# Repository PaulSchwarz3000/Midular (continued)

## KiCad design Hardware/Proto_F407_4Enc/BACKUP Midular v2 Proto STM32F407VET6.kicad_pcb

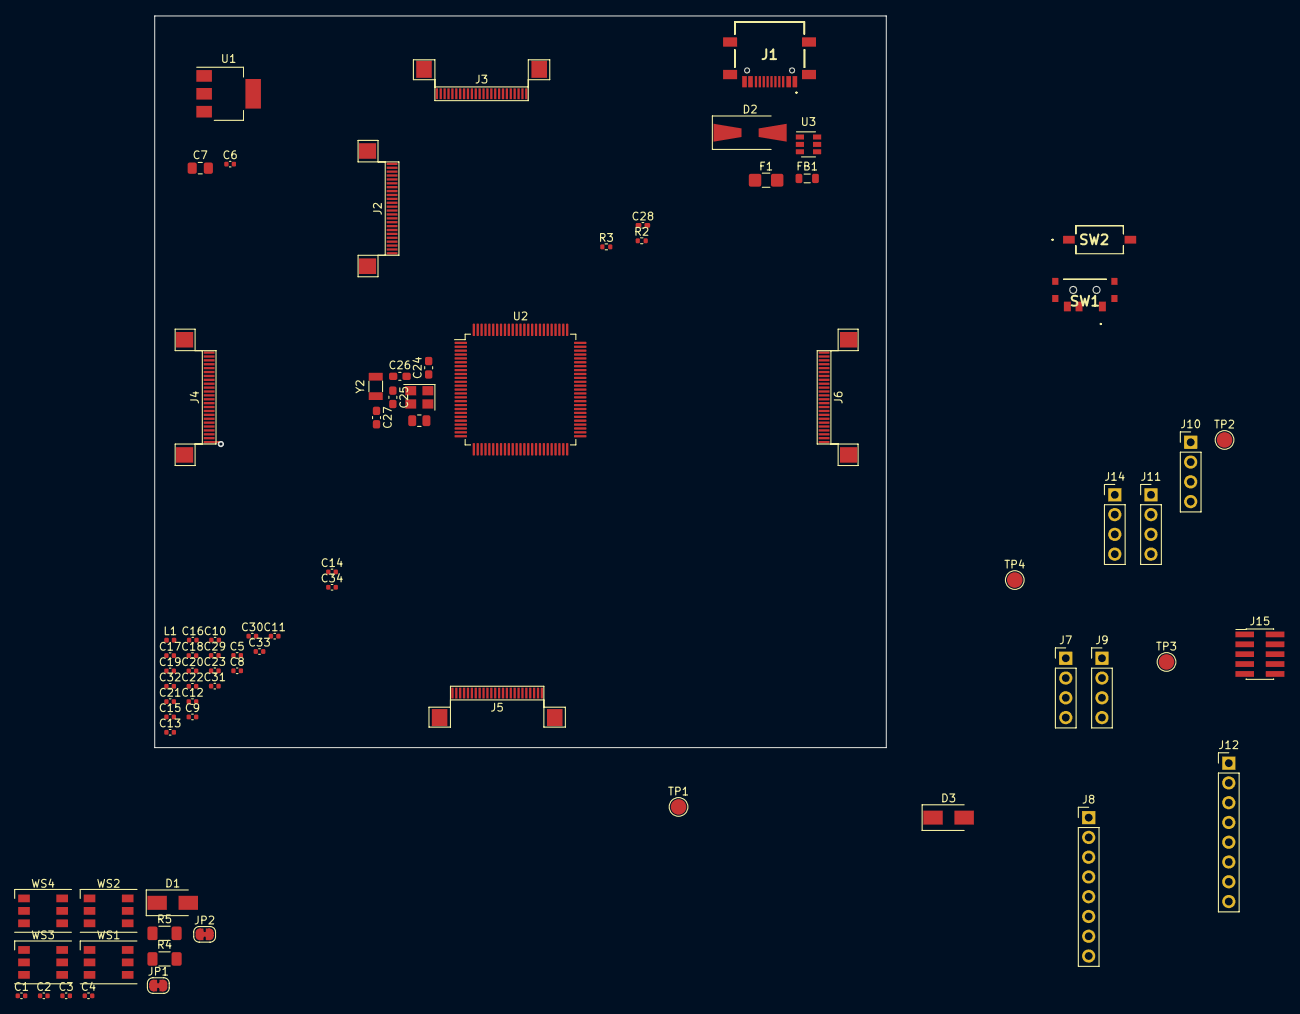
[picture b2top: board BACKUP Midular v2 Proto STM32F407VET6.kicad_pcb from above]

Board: 4 copper layers, 94.0 x 94.0 mm, 77 parts (1 on the bottom side), 75 nets.

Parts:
BAT1: CR2032-BS-6-1; CR2032BS61
C1, C2, C3, C4, C5, C9, C12, C16, C18, C20, C22, C29, C31: 100n; C_0402_1005Metric
C6, C8, C10, C11, C33, C34: 2u2; C_0402_1005Metric
C7: 10uF; C_0805_2012Metric_Pad1.18x1.45mm_HandSolder
C13, C15, C17, C19, C21, C23, C30: 10n; C_0402_1005Metric
C14: 1u; C_0402_1005Metric
C24, C25, C26, C27: 12p; C_0603_1608Metric_Pad1.08x0.95mm_HandSolder
C28: 10n; C_0402_1005Metric_Pad0.74x0.62mm_HandSolder
C32: 4u7; C_0402_1005Metric
D1: NC; D_SMA
D2: D_Schottky; D_SMA-SMB_Universal_Handsoldering
D3: M7; D_SMA
F1: Polyfuse 500mA; Fuse_1206_3216Metric_Castellated
FB1: GZ2012D601TF; L_0805_2012Metric
J1: USB_C_Receptacle_USB2.0; TYPEC304SACP16
J2, J3, J4, J5, J6: Conn_01x24; FPC_24_AFC24-S24FIC-00
J7, J9, J10, J11, J14: Conn_01x04; PinHeader_1x04_P2.54mm_Vertical
J8, J12: Conn_01x08; PinHeader_1x08_P2.54mm_Vertical
J15: Conn_ARM_JTAG_SWD_10; PinHeader_2x05_P1.27mm_Vertical_SMD
JP1, JP2: SolderJumper_2_Bridged; SolderJumper-2_P1.3mm_Bridged_RoundedPad1.0x1.5mm
L1: 39n; L_0402_1005Metric
R1: 220R; R_0805_2012Metric
R2, R3: 10k; R_0402_1005Metric
R4, R5: 1k1; R_1206_3216Metric_Pad1.30x1.75mm_HandSolder
SW1: SW_SPDT; SK3296S01L3
SW2: SW_SPST; K21107STA4SW06
TP1, TP2, TP3, TP4: TestPoint; TestPoint_Pad_D2.0mm
U1: AMS1117-3.3; SOT-223-3_TabPin2
U2: STM32F407VETx; LQFP-100_14x14mm_P0.5mm
U3: USBLC6-2SC6; SOT-23-6
WS1, WS2, WS3, WS4: WS2813; LED_WS2812_PLCC6_5.0x5.0mm_P1.6mm
Y1: 25MHz 12pF; Crystal_SMD_3225-4Pin_3.2x2.5mm
Y2: 32.768 kHz; Crystal_SMD_3215-2Pin_3.2x1.5mm

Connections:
+3V3: C7.1, C8.1, C15.2, C16.2, C17.2, C18.2, C19.2, C20.2, C21.2, C22.2, C23.2, C29.2, C30.2, C31.2, C32.2, C33.1, C34.1, J2.3, J2.22, J7.3, J8.2, J10.3, J11.3, J14.3, J15.1, JP1.1, L1.1, R3.2, SW1.1, TP3.1, U1.2, U2.11, U2.19, U2.28, U2.50, U2.75, U2.100
+5V: C5.1, C6.1, D1.2, D2.1, D3.2, J2.1, J2.24, J3.6, J3.7, J3.18, J3.19, J4.6, J4.7, J4.18, J4.19, J5.6, J5.7, J5.18, J5.19, J6.6, J6.7, J6.18, J6.19, J9.4, J12.8, JP2.1, TP4.1, U1.3, U3.5
+12V: J3.2, J3.4, J3.21, J3.23, J4.2, J4.4, J4.21, J4.23, J5.2, J5.4, J5.21, J5.23, J6.2, J6.4, J6.21, J6.23
BOOT0: R2.1, U2.94
CAN_Rx: J7.1, U2.81
CAN_Tx: J7.4, U2.82
CRx2: J4.16, U2.33
CRx3: J5.16, U2.57
CRx4: J6.16, U2.62
CTx1: J3.9, U2.90
CTx2: J4.9, U2.16
CTx3: J5.9, U2.54
CTx4: J6.9, U2.61
DAC_OUT1: J14.1, U2.29
DAC_OUT2: J14.4, U2.30
ENC1_A: J2.4, U2.77
ENC1_B: J2.6, U2.89
ENC2_A: J2.8, U2.31
ENC2_B: J2.10, U2.32
ENC3_A: J2.15, U2.59
ENC3_B: J2.17, U2.60
ENC4_A: J2.19, U2.23
ENC4_B: J2.21, U2.24
GND: BAT1.2, C1.1, C2.1, C3.1, C4.1, C5.2, C6.2, C7.2, C8.2, C9.2, C10.2, C11.2, C12.2, C13.2, C14.2, C15.1, C16.1, C17.1, C18.1, C19.1, C20.1, C21.1, C22.1, C23.1, C24.2, C25.2, C26.2, C27.2, C28.2, C29.1, C30.1, C31.1, C32.1, C33.2, C34.2, J1.A1, J1.A12, J1.B1, J1.B12, J2.2, J2.7, J2.11, J2.14, J2.18, J2.23, J3.1, J3.3, J3.5, J3.8, J3.10, J3.12, J3.13, J3.15, J3.17, J3.20, J3.22, J3.24, J4.1, J4.3, J4.5, J4.8, J4.10, J4.12, J4.13, J4.15, J4.17, J4.20, J4.22, J4.24, J5.1, J5.3, J5.5, J5.8, J5.10, J5.12, J5.13, J5.15, J5.17, J5.20, J5.22, J5.24, J6.1, J6.3, J6.5, J6.8, J6.10, J6.12, J6.13, J6.15, J6.17, J6.20, J6.22, J6.24, J7.2, J8.1, J9.2, J10.2, J11.2, J12.2, J12.4, J12.6, J14.2, J15.3, J15.5, J15.9, SW1.3, SW2.2, TP2.1, U1.1, U2.10, U2.20, U2.27, U2.74, U2.99, U3.2, WS1.5, WS2.5, WS3.5, WS4.5, Y1.2, Y1.4
HSE_IN: C24.1, U2.12, Y1.1
HSE_OUT: R1.1, U2.13
I2C2_SCL: J10.1, R4.1, U2.47
I2C2_SDA: J10.4, R5.2, U2.48
I2S2_CK: J12.5, U2.52
I2S2_SD: J12.1, U2.18
I2S2_WS: J12.7, U2.51
I2S2_ext_SD: J12.3, U2.17
LCD_CS: J8.7, U2.97
LCD_DC: J8.6, U2.98
LSE_IN: C26.1, U2.8, Y2.1
LSE_OUT: C27.1, U2.9, Y2.2
NRST: C28.1, J8.5, J15.10, R3.1, SW2.1, U2.14
unnamed: C25.1, R1.2, Y1.3
unnamed: D2.2, F1.1
unnamed: D3.1, J9.1
unnamed: F1.2, FB1.1
unnamed: JP1.2, R4.2, R5.1
unnamed: R2.2, SW1.2
unnamed: WS1.3, WS2.4, WS3.6
unnamed: WS2.3, WS3.4, WS4.6
RCC_MCO: TP1.1, U2.67
SPI3_MISO: J8.4, U2.79
SPI3_MOSI: J8.8, U2.91
SPI3_SCK: J8.3, U2.78
SWCLK: J15.4, U2.76
SWDIO: J15.2, U2.72
UART_Rx: J11.1, U2.83
UART_Tx: J11.4, U2.80
URx1: J3.14, U2.93
URx2: J4.14, U2.26
URx3: J5.14, U2.56
URx4: J6.14, U2.64
USB_CONN_D+: J1.A6, J1.B6, U3.4
USB_CONN_D-: J1.A7, J1.B7, U3.6
USB_D+: U2.71, U3.3
USB_D-: U2.70, U3.1
UTx1: J3.11, U2.92
UTx2: J4.11, U2.25
UTx3: J5.11, U2.55
UTx4: J6.11, U2.63
VBAT: BAT1.1, U2.6
VBUS: FB1.2, J1.A4, J1.A9, J1.B4, J1.B9, U2.68
VCAP_1: C9.1, C10.1, U2.49
VCAP_2: C11.1, C12.1, U2.73
VDDA: C13.1, C14.1, L1.2, U2.21, U2.22
VWS2812: C1.2, C2.2, C3.2, C4.2, D1.1, JP2.2, WS1.2, WS2.2, WS3.2, WS4.2
WS2812_A: U2.65, WS1.4, WS1.6, WS2.6
WS2812_B: J9.3, U2.66
WS2812_CONN_BI: J2.13, WS3.3, WS4.4
WS2812_CONN_DIN: J2.12, WS4.3

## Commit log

2021-03-02 F407_4Enc Initial commit
2021-03-02 included csv and xml files
2021-03-02 Added KiCad libs/footprints/scripts
2021-03-03 minor label changes in schematic, added schematic + board image plots
